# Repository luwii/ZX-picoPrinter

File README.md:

# ZX-picoPrinter

**ZX-picoPrinter** is a modern hardware emulator and DIY replacement for the vintage Sinclair ZX Printer. Built around a custom circuit board and a Raspberry Pi Pico 2, it restores native printing capabilities to the ZX Spectrum by translating legacy signals for modern thermal POS printers and optional display screens.

https://github.com/user-attachments/assets/f9424bd6-6a39-4c2c-87f9-4fa740e79a30

---

## Key Features

- **Full Command Compatibility**: Works seamlessly with native ZX Spectrum Sinclair BASIC commands, including `LPRINT`, `LLIST`, and `COPY`.

- **Thermal POS Printing**: Outputs directly to standard, cost-effective thermal receipt printers via a serial connection.

- **Optional Preview Display**: Real-time on-screen display of print jobs.

- **Modular Hardware Design**: The display screen and thermal printer operate independently—you can run either device alone or both simultaneously.

---

## Hardware Requirements

- **Microcontroller**: Raspberry Pi Pico 2

- **Printer**: Compatible thermal POS receipt printer

- **Power**: Dedicated power supply matching your thermal printer's specifications (usually you need a lot of current)

- **Interface**: Custom ZX-picoPrinter circuit board and associated logic ICs

- **Cables**: USB connection cable to program the pico.

- **Display (*Optional*)**: Supported screen module for print previews

---

## Getting Started

### 1. Prerequisites

Install your preferred development environment for the Raspberry Pi Pico[cite: 1]. (This project was developed using **Visual Studio Code** with the official **Raspberry Pi Pico Extension**).

### 2. Clone the Repository

```bash

git clone [https://github.com/luwii/ZX-picoPrinter.git](https://github.com/luwii/ZX-picoPrinter.git)

```

### 3. Assemble and Wire Hardware

Assemble the custom PCB, install the logic chips, and complete the wiring following the diagrams in the [Documentation](https://github.com/luwii/ZX-picoPrinter/blob/main/Documentation/zxpicoprinter.pdf).

> **Note**: The display screen and thermal printer operate independently; you only need to connect the output device(s) you plan to use.

### 4. Flash the Firmware

Build and upload the provided firmware to the Raspberry Pi Pico using your IDE or by copying the compiled `.uf2` file.

### 5. Verify and Test

Power on the ZX Spectrum and verify functionality by executing:

```basic

LPRINT "ZX-picoPrinter Ready"

```

---

## Documentation & Resources

- [ZX-picoPrinter Manual (PDF)](https://github.com/luwii/ZX-picoPrinter/blob/main/Documentation/zxpicoprinter.pdf)[cite: 1]

- [Official Raspberry Pi Pico Documentation](https://www.raspberrypi.com/documentation/microcontrollers/pico-series.html)[cite: 1]

---

## License

This project is open-source software licensed under the [MIT License](LICENSE).

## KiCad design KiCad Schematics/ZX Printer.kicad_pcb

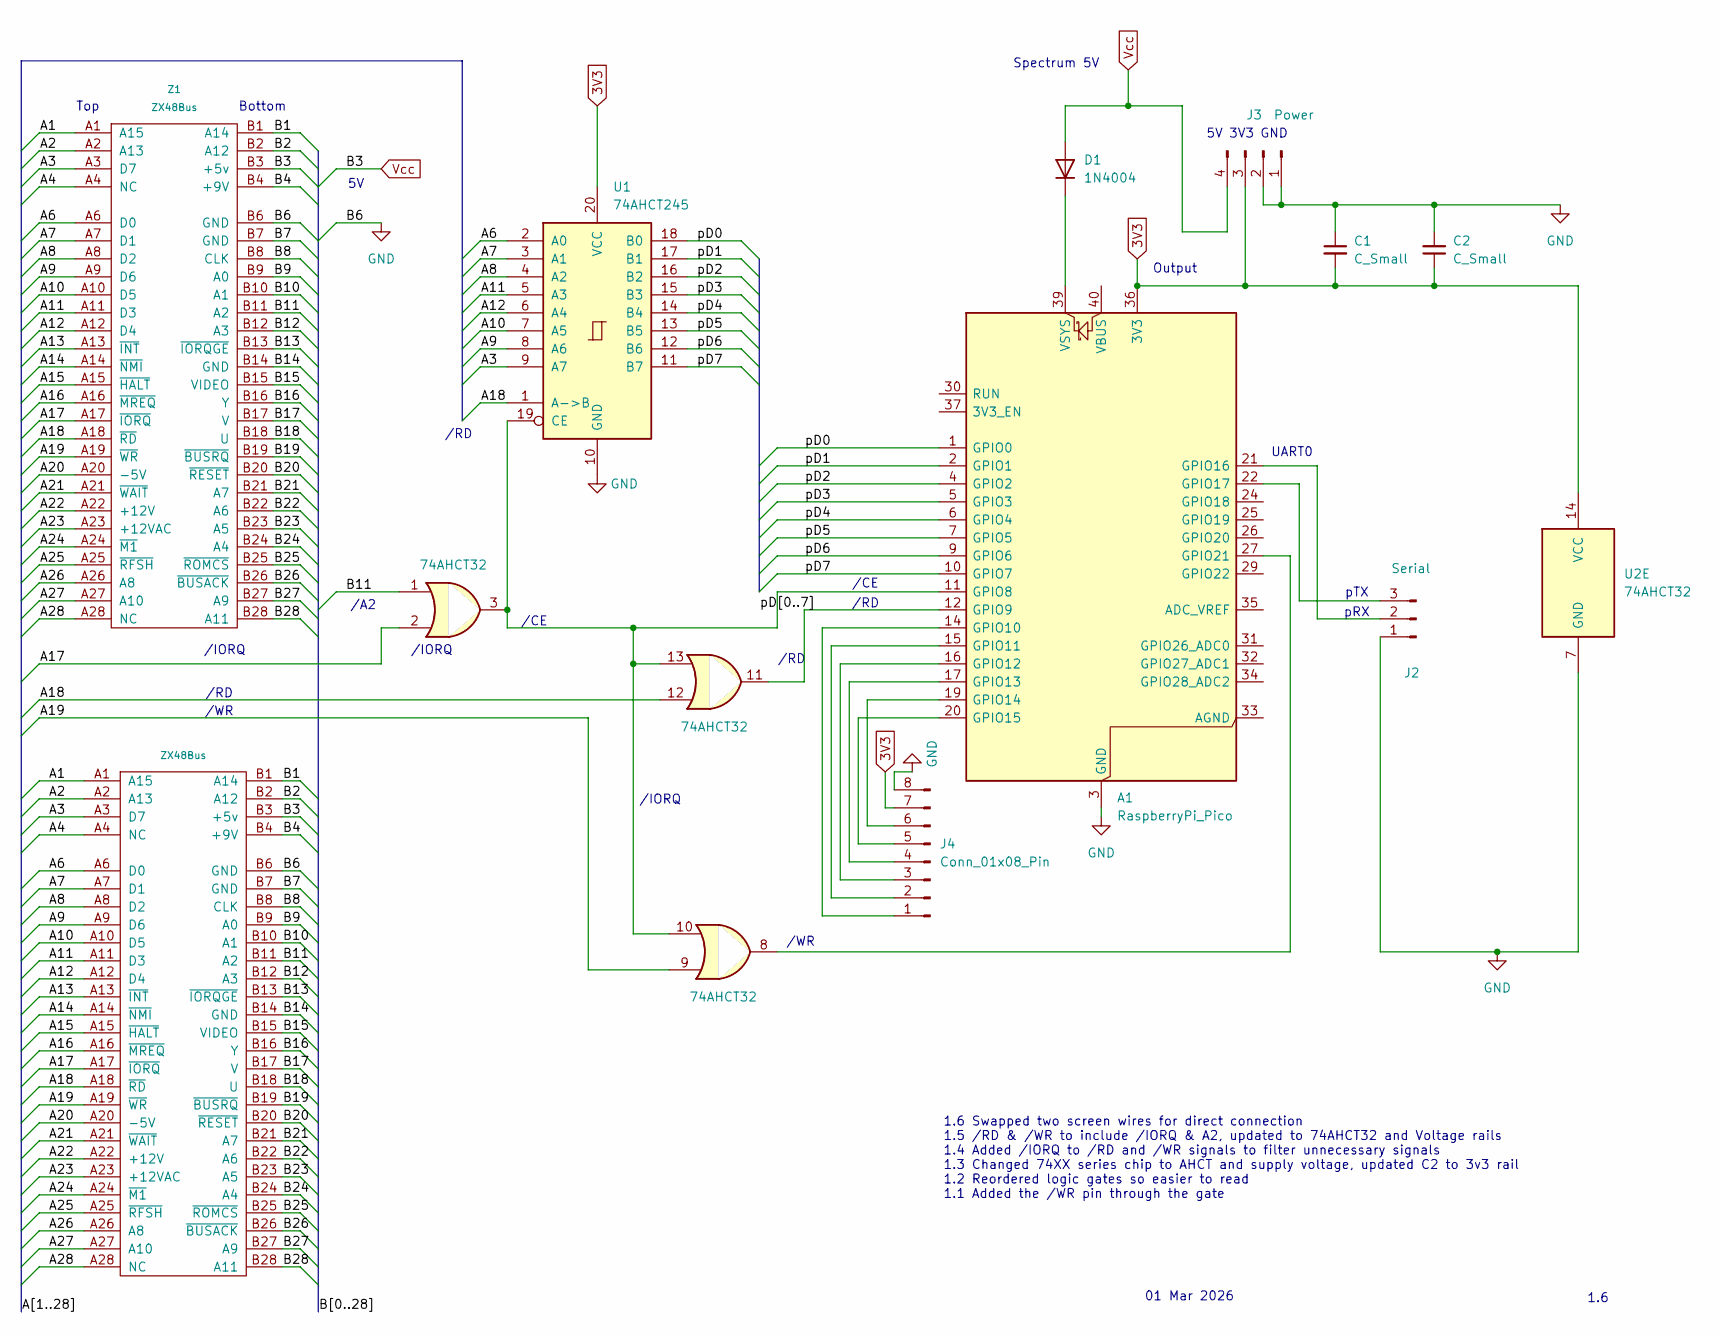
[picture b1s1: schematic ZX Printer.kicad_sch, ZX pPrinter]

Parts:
A1: RaspberryPi_Pico; RaspberryPi_Pico_Common_Unspecified
C1, C2: C_Small; C_Disc_D3.8mm_W2.6mm_P2.50mm
D1: 1N4004; D_DO-41_SOD81_P10.16mm_Horizontal
J2: Serial; PinHeader_1x03_P2.54mm_Vertical
J3: Power; PinHeader_1x04_P2.54mm_Vertical
J4: Conn_01x08_Pin; PinHeader_1x08_P2.54mm_Vertical
U1: 74AHCT245; DIP-20_W7.62mm
U2: 74AHCT32; CERDIP-14_W7.62mm_SideBrazed
Z1: ZX48Bus; ZX_Bus_Edge_Connector
Z2: ZX48Bus; ZX_Bus_Pin_Header

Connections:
3V3: A1.36 (3V3), C1.2, C2.1, J3.3, J4.7, U1.20 (VCC), U2.14 (VCC)
/A1: Z1.A1 (A15), Z2.A1 (A15)
/A2: Z1.A2 (A13), Z2.A2 (A13)
/A3: U1.9 (A7), Z1.A3 (D7), Z2.A3 (D7)
/A4: Z1.A4 (NC), Z2.A4 (NC)
/A6: U1.2 (A0), Z1.A6 (D0), Z2.A6 (D0)
/A7: U1.3 (A1), Z1.A7 (D1), Z2.A7 (D1)
/A8: U1.4 (A2), Z1.A8 (D2), Z2.A8 (D2)
/A9: U1.8 (A6), Z1.A9 (D6), Z2.A9 (D6)
/A10: U1.7 (A5), Z1.A10 (D5), Z2.A10 (D5)
/A11: U1.5 (A3), Z1.A11 (D3), Z2.A11 (D3)
/A12: U1.6 (A4), Z1.A12 (D4), Z2.A12 (D4)
/A13: Z1.A13 (~INT), Z2.A13 (~INT)
/A14: Z1.A14 (~NMI), Z2.A14 (~NMI)
/A15: Z1.A15 (~HALT), Z2.A15 (~HALT)
/A16: Z1.A16 (~MREQ), Z2.A16 (~MREQ)
/A17: U2.2, Z1.A17 (~IORQ), Z2.A17 (~IORQ)
/A18: U1.1 (A->B), U2.12, Z1.A18 (~RD), Z2.A18 (~RD)
/A19: U2.9, Z1.A19 (~WR), Z2.A19 (~WR)
/A20: Z1.A20 (-5V), Z2.A20 (-5V)
/A21: Z1.A21 (~WAIT), Z2.A21 (~WAIT)
/A22: Z1.A22 (+12V), Z2.A22 (+12V)
/A23: Z1.A23 (+12VAC), Z2.A23 (+12VAC)
/A24: Z1.A24 (~M1), Z2.A24 (~M1)
/A25: Z1.A25 (~RFSH), Z2.A25 (~RFSH)
/A26: Z1.A26 (A8), Z2.A26 (A8)
/A27: Z1.A27 (A10), Z2.A27 (A10)
/A28: Z1.A28 (NC), Z2.A28 (NC)
/B1: Z1.B1 (A14), Z2.B1 (A14)
/B2: Z1.B2 (A12), Z2.B2 (A12)
/B4: Z1.B4 (+9V), Z2.B4 (+9V)
/B7: Z1.B7 (GND), Z2.B7 (GND)
/B8: Z1.B8 (CLK), Z2.B8 (CLK)
/B9: Z1.B9 (A0), Z2.B9 (A0)
/B10: Z1.B10 (A1), Z2.B10 (A1)
/B11: U2.1, Z1.B11 (A2), Z2.B11 (A2)
/B12: Z1.B12 (A3), Z2.B12 (A3)
/B13: Z1.B13 (~IORQGE), Z2.B13 (~IORQGE)
/B14: Z1.B14 (GND), Z2.B14 (GND)
/B15: Z1.B15 (VIDEO), Z2.B15 (VIDEO)
/B16: Z1.B16 (Y), Z2.B16 (Y)
/B17: Z1.B17 (V), Z2.B17 (V)
/B18: Z1.B18 (U), Z2.B18 (U)
/B19: Z1.B19 (~BUSRQ), Z2.B19 (~BUSRQ)
/B20: Z1.B20 (~RESET), Z2.B20 (~RESET)
/B21: Z1.B21 (A7), Z2.B21 (A7)
/B22: Z1.B22 (A6), Z2.B22 (A6)
/B23: Z1.B23 (A5), Z2.B23 (A5)
/B24: Z1.B24 (A4), Z2.B24 (A4)
/B25: Z1.B25 (~ROMCS), Z2.B25 (~ROMCS)
/B26: Z1.B26 (~BUSACK), Z2.B26 (~BUSACK)
/B27: Z1.B27 (A9), Z2.B27 (A9)
/B28: Z1.B28 (A11), Z2.B28 (A11)
/pD0: A1.1 (GPIO0), U1.18 (B0)
/pD1: A1.2 (GPIO1), U1.17 (B1)
/pD2: A1.4 (GPIO2), U1.16 (B2)
/pD3: A1.5 (GPIO3), U1.15 (B3)
/pD4: A1.6 (GPIO4), U1.14 (B4)
/pD5: A1.7 (GPIO5), U1.13 (B5)
/pD6: A1.9 (GPIO6), U1.12 (B6)
/pD7: A1.10 (GPIO7), U1.11 (B7)
GND: A1.3 (GND), A1.8 (GND), A1.13 (GND), A1.18 (GND), A1.23 (GND), A1.28 (GND), A1.38 (GND), C1.1, C2.2, J2.1, J3.1, J3.2, J4.8, U1.10 (GND), U2.7 (GND), Z1.B6 (GND), Z2.B6 (GND)
unnamed: A1.11 (GPIO8), U1.19 (CE), U2.3, U2.10, U2.13
unnamed: A1.12 (GPIO9), U2.11
unnamed: A1.14 (GPIO10), J4.1
unnamed: A1.15 (GPIO11), J4.2
unnamed: A1.16 (GPIO12), J4.3
unnamed: A1.17 (GPIO13), J4.4
unnamed: A1.19 (GPIO14), J4.6
unnamed: A1.20 (GPIO15), J4.5
unnamed: A1.21 (GPIO16), J2.2
unnamed: A1.22 (GPIO17), J2.3
unnamed: A1.27 (GPIO21), U2.8
unnamed: A1.39 (VSYS), D1.1 (K)
Vcc: D1.2 (A), J3.4, Z1.B3 (+5v), Z2.B3 (+5v)

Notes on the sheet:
3V3
/IORQ
UART0
Bottom
/WR
/RD
1.6
/CE
Top
Spectrum 5V
GND
Output
/A2
pTX
01 Mar 2026
1.6 Swapped two screen wires for direct connection 1.5 /RD & /WR to include /IORQ & A2, updated to 74AHCT32 and Voltage rails 1.4 Added /IORQ to /RD and /WR signals to filter unnecessary signals 1.3 Changed 74XX series chip to AHCT and supply voltage, updated C2 to 3v3 rail 1.2 Reordered logic gate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
pRX

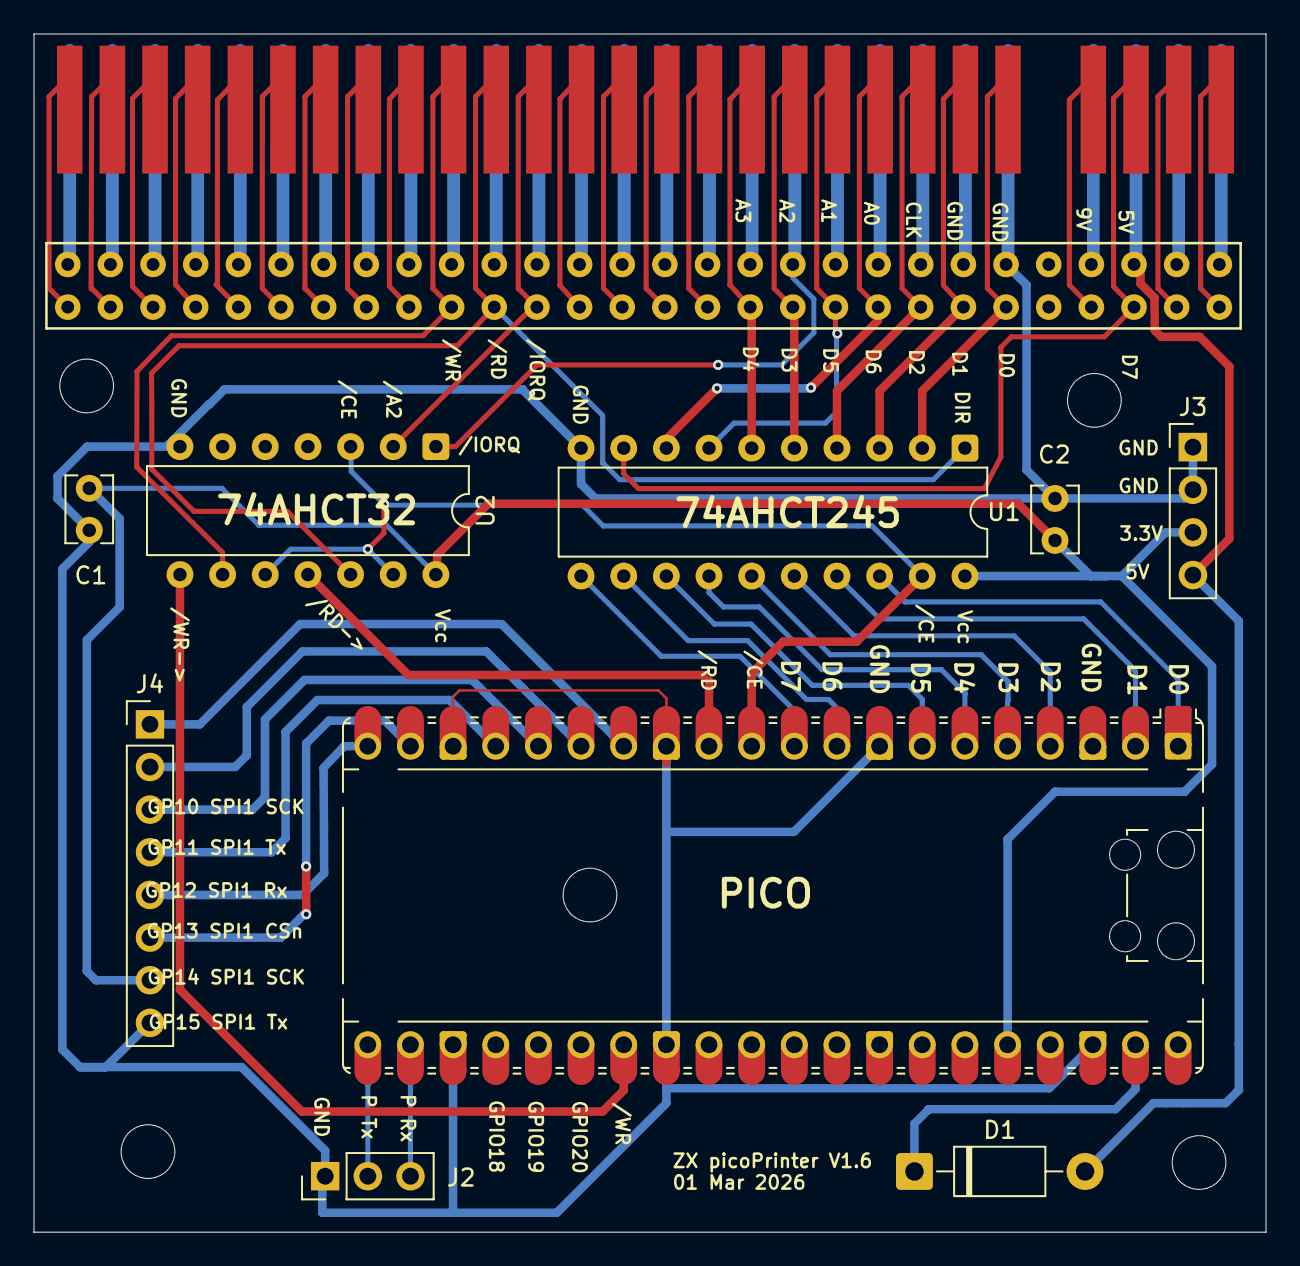
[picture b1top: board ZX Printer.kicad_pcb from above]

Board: 2 copper layers, 73.4 x 71.4 mm, 11 parts (0 on the bottom side), 75 nets.

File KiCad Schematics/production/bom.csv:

Designator,Footprint,Quantity,Value,LCSC Part #
A1,RaspberryPi_Pico_Common_Unspecified,1,RaspberryPi_Pico,
"C1, C2",C_Disc_D3.8mm_W2.6mm_P2.50mm,2,C_Small,
D1,D_DO-41_SOD81_P10.16mm_Horizontal,1,1N4004,
J2,PinHeader_1x03_P2.54mm_Vertical,1,Serial,
J3,PinHeader_1x04_P2.54mm_Vertical,1,Power,
J4,PinHeader_1x08_P2.54mm_Vertical,1,Conn_01x08_Pin,
U1,DIP-20_W7.62mm,1,74AHCT245,
U2,CERDIP-14_W7.62mm_SideBrazed,1,74AHCT32,
Z1,ZX_Bus_Edge_Connector,1,ZX48Bus,
Z2,ZX_Bus_Pin_Header,1,ZX48Bus,

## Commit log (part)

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2026-02-15 Create Hardware
2026-02-15 Fix spelling errors and add project description
    Correct spelling errors and add project context.
2026-02-15 Delete ZX Printer.kicad_pcb
    Moved to Hardware folder
2026-02-15 Delete ZX Printer.kicad_pro
    Moved to Hardware folder
2026-02-15 Delete ZX Printer.kicad_sch
    Moved to Hardware folder
2026-02-15 Enhance README with detailed project description
    Expanded project description to clarify functionality and components used.
2026-02-15 Create Software
2026-02-15 Create Documentation
2026-02-15 Create test
2026-03-01 V1.6
2026-03-01 Fixed mounting holes
2026-03-01 Added Software description and version history
2026-03-01 Add source link for zxbus connector
    Added link to the original repository for the connector.
2026-03-01 Update README.md with original repo link
    Added a reference to the original repository for the connector.
2026-03-01 Updated README.md with improved project information.
2026-03-01 Revise README.md for clarity and detail
    Updated project description and features, added hardware requirements, and refined getting started guide.
2026-03-01 Updated references
    Updated documentation references in README.md
2026-03-01 Create .gitignore file with content for KiCad, C/Embedded development, IDE files, and OS files
2026-05-18 Add files via upload
    Compiled Pico2 printer
